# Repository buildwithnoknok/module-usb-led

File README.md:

# noknok LEDs

A USB-controlled ring of 8 WS2812b RGB LEDs for the noknok ecosystem. The Raspberry Pi
Pico drives it as a **USB host**; it can also be driven directly from a PC.

## Features
- 8× WS2812b RGB LEDs (ring)
- CH32V203G6U6 microcontroller, USB 1.1 (CDC) device
- USB-C power + data; 2× Qwiic / STEMMA QT compatible I2C pass-through connectors
- **Unique per-unit USB serial** derived from the chip UID — so the Conductor can tell
  identical modules apart and map them to roles (the USB counterpart of the I2C UID)
- Rich control: per-LED colour/brightness/timed-off in one command, plus 6 built-in
  animations (rainbow, breathe, theatre chase, colour wipe, twinkle, sundown)

## Status
- **Firmware: v1.8.2 — complete** (see [firmware/readme.md](firmware/readme.md) for the
  full command protocol, flashing instructions, and version history)
- Hardware: v1.0

## How it's controlled

### From a Raspberry Pi Pico (USB host) — the noknok Conductor
The Pico hosts the module over PIO-USB (D+ → GP16, D− → GP17, behind a **powered** hub
such as the DataHub). The `NoknokLEDs` driver lives in
[`brain-Pico/software/noknok_usb.py`](https://github.com/buildwithnoknok/brain-Pico/tree/main/software)
and is discovered by the Conductor:

```python
from noknok import Conductor

c = Conductor()
c.enumerate_usb()          # brings up the USB host port, finds all LED modules
# (use c.enumerate_all() for a product that mixes I2C + USB modules)

leds = c.leds[0]                                  # or c.by_uid("<serial>"), or c.role["lamp"]
leds.set_all(255, 0, 0)                           # all red
leds.set_pixel(3, 0, 255, 0)                      # LED 3 green
leds.set_brightness(128)                          # global brightness
leds.set_led(0xFF, 0, 0, 255, brightness=200, duration_ms=1000)  # all blue 1 s, then off
leds.play_preset(leds.PRESET_RAINBOW, speed=40)  # non-blocking animation on the module
leds.play_preset(leds.PRESET_SUNDOWN, speed=30, r=0, g=0, b=255)  # 30 min fade to off, blue
leds.off()
```

Each module carries a unique serial, so multiple LED modules on one hub are addressed
individually. See **[Ecosystem → enumeration.md](https://github.com/buildwithnoknok/Ecosystem/blob/main/software/enumeration.md)**
(USB Module Discovery & Identity) and **[roles.md](https://github.com/buildwithnoknok/Ecosystem/blob/main/software/roles.md)**
(role assignment — this is an *output* module, assigned by cue-and-confirm).

### From a PC
PowerShell / Python helpers in [`tools/`](tools) (`noknok_leds.ps1`, `noknok_leds_pc.py`)
auto-detect the module and expose the same commands.

## Repository Structure
- `/hardware` — KiCad files, schematics, 3D models
- `/firmware` — source (`src/`), built binaries (`bin/`), and the firmware change record (`readme.md`)
- `/tools` — PC control scripts

---

## Trademarks

**noknok** is a registered trademark in Switzerland (Swissreg 1300007033).

Qwiic is a registered trademark of SparkFun Electronics, Inc. STEMMA QT is a
trademark of Adafruit Industries, LLC. Both are named here only to state
connector compatibility - noknok is not affiliated with, endorsed by, or
sponsored by either company.

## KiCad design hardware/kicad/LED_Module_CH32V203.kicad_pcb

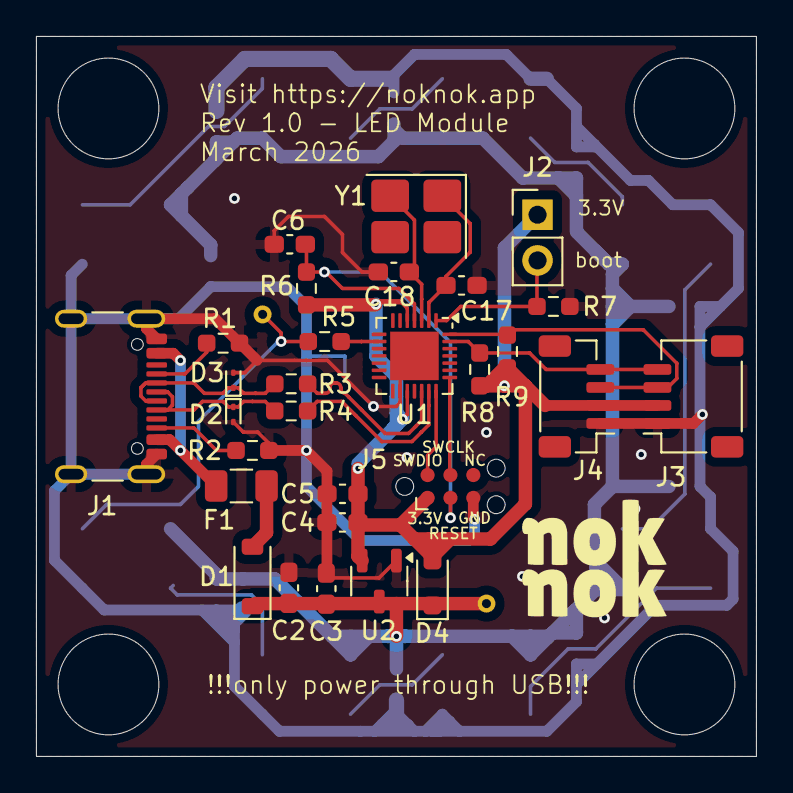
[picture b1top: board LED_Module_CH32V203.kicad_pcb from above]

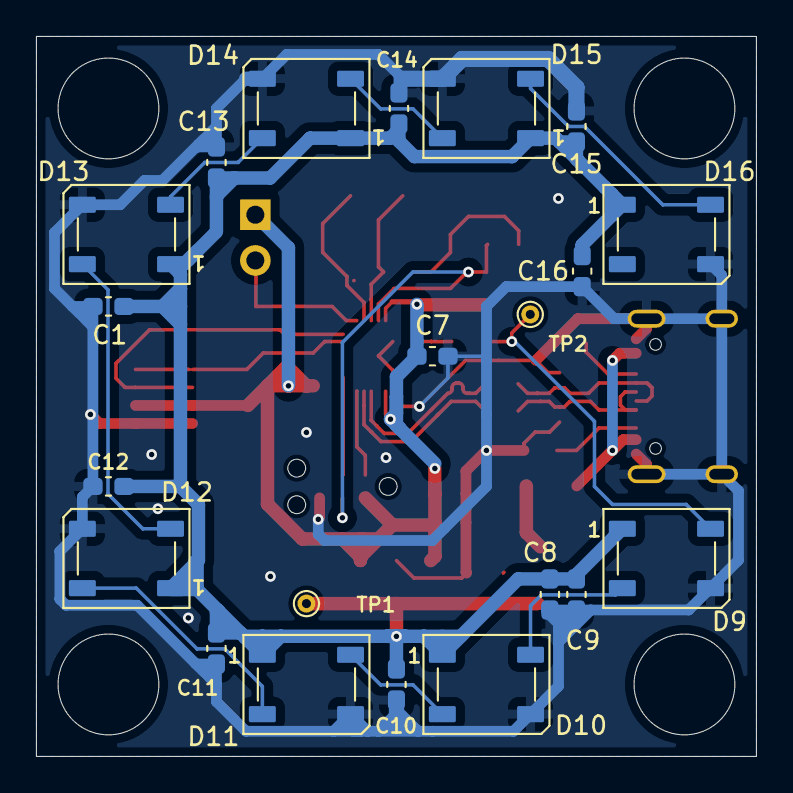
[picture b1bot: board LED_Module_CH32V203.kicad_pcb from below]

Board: 2 copper layers, 40.0 x 40.0 mm, 50 parts (21 on the bottom side), 26 nets.

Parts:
C1, C2, C5, C8: 10uF; C_0603_1608Metric_Pad1.08x0.95mm_HandSolder
C3, C4, C7: 1uF; C_0603_1608Metric_Pad1.08x0.95mm_HandSolder
C6, C9, C10, C11, C12, C13, C14, C15, C16: 0.1uF; C_0603_1608Metric_Pad1.08x0.95mm_HandSolder
C17, C18: 18pF; C_0603_1608Metric_Pad1.08x0.95mm_HandSolder
D1: 1N4007; D_SOD-123
D2, D3: ESD9B5.0ST5G; D_SOD-923
D4: D_Schottky; D_SOD-323_HandSoldering
D9, D10, D11, D12, D13, D14, D15, D16: WS2812B; LED_WS2812B_PLCC4_5.0x5.0mm_P3.2mm
F1: Resettable Polyfuse; Fuse_1206_3216Metric
J1: USB_C_Receptacle_USB2.0_16P; USB_C_Receptacle_GCT_USB4105-xx-A_16P_TopMnt_Horizontal
J2: Jumper Cap; PinHeader_1x02_P2.54mm_Vertical
J3: Qwiic / StemmaQT Connector; JST_SH_SM04B-SRSS-TB_1x04-1MP_P1.00mm_Horizontal_CHRIS
J4: Qwiic / StemmaQT Connector; JST_SH_BM04B-SRSS-TB_1x04-1MP_P1.00mm_Vertical
J5: TagConnect_TC2030; Tag-Connect_TC2030-IDC-NL_2x03_P1.27mm_Vertical
R1, R2: 5.1k; R_0603_1608Metric_Pad0.98x0.95mm_HandSolder
R3, R4: 22R; R_0603_1608Metric_Pad0.98x0.95mm_HandSolder
R5: 100R; R_0603_1608Metric_Pad0.98x0.95mm_HandSolder
R6, R7: 10k; R_0603_1608Metric_Pad0.98x0.95mm_HandSolder
R8, R9: 4.7k; R_0603_1608Metric_Pad0.98x0.95mm_HandSolder
TP1, TP2: TestPoint; TestPoint_THTPad_D1.0mm_Drill0.5mm
U1: CH32V203G6U6; WQFN-28-1EP_4x4mm_P0.4mm_EP2.7x2.7mm
U2: XC6206P332MR; SOT-23-3
Y1: Crystal; Crystal_SMD_3225-4Pin_3.2x2.5mm_HandSoldering

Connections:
+3.3V: C4.1, C5.1, C7.1, D4.2 (A), J2.1, J3.2, J4.2, J5.1 (VCC), R6.2, R8.2, R9.2, U1.5 (VDDA), U1.17 (VDD), U2.2 (VO)
+4.1V: C1.1, C2.1, C3.1, C8.1, C9.1, C10.1, C11.1, C12.1, C13.1, C14.1, C15.1, C16.1, D1.1 (K), D4.1 (K), D9.1 (VDD), D10.1 (VDD), D11.1 (VDD), D12.1 (VDD), D13.1 (VDD), D14.1 (VDD), D15.1 (VDD), D16.1 (VDD), TP1.1, U2.3 (VI)
+5V: D1.2 (A), F1.1
D+: D2.1 (A1), J1.A6 (D+), J1.B6 (D+), R4.1, R4.2, U1.20 (PA12/USB_D+)
D-: D3.1 (A1), J1.A7 (D-), J1.B7 (D-), R3.1, R3.2, U1.19 (PA10/PA11/USB_D-)
GND: C1.2, C2.2, C3.2, C4.2, C5.2, C6.1, C7.2, C8.2, C9.2, C10.2, C11.2, C12.2, C13.2, C14.2, C15.2, C16.2, C17.1, C18.1, D2.2 (A2), D3.2 (A2), D9.3 (VSS), D10.3 (VSS), D11.3 (VSS), D12.3 (VSS), D13.3 (VSS), D14.3 (VSS), D15.3 (VSS), D16.3 (VSS), J1.A1 (GND), J1.A12 (GND), J1.B1 (GND), J1.B12 (GND), J1.S1 (SHIELD), J3.1, J4.1, J5.5 (GND), R1.1, R2.1, R7.2, U1.16 (VSS), U1.29 (VSS), U2.1 (GND)
unnamed: D9.4 (DIN), R5.1, TP2.1
unnamed: D9.2 (DOUT), D10.4 (DIN)
unnamed: D10.2 (DOUT), D11.4 (DIN)
unnamed: D11.2 (DOUT), D12.4 (DIN)
unnamed: D12.2 (DOUT), D13.4 (DIN)
unnamed: D13.2 (DOUT), D14.4 (DIN)
unnamed: D14.2 (DOUT), D15.4 (DIN)
unnamed: D15.2 (DOUT), D16.4 (DIN)
unnamed: F1.2, J1.A4 (VBUS), J1.A9 (VBUS), J1.B4 (VBUS), J1.B9 (VBUS)
unnamed: J1.A5 (CC1), R1.2
unnamed: J1.B5 (CC2), R2.2
unnamed: J2.2, R7.1, U1.1 (BOOT0/PB8)
unnamed: J3.3, J4.3, R9.1, U1.28 (PB7)
unnamed: J3.4, J4.4, R8.1, U1.27 (PB6)
unnamed: J5.4 (SWCLK), U1.22 (PA14/SWCLK)
unnamed: J5.2 (SWDIO), U1.21 (PA13/SWDIO)
unnamed: C6.2, J5.3 (~RESET), R6.1, U1.4 (~RST)
unnamed: C17.2, U1.2 (OSC_IN/PD0), Y1.1
unnamed: C18.2, U1.3 (OSC_OUT/PD1), Y1.2
unnamed: R5.2, U1.9 (PA3)

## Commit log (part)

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2026-05-08 Create hardware folder
2026-05-08 Create firmware folder
2026-05-08 Create docs folder
2026-05-08 Create hardware/kicad folder
2026-05-08 Create firmware/src folder
2026-05-08 Create firmware/bin folder
2026-06-01 Update product name to # noknok LEDs
2026-06-02 Add firmware v1.0 and PC helper
2026-06-02 Fix ws_show: replace ISR with polling (DMA TC flag)
2026-06-02 Fix USB: use 144MHz HSI (fsusb requires 144/96/48MHz), fix WS2812b timing
2026-06-02 Fix: enable AFIO clock (PA3 AF), add SWEVGR trigger, remove boot flash for USB test
2026-06-02 firmware: v1.1 - interrupt DMA, 144 MHz, AFIO fix, boot flash
2026-06-02 firmware: update hex to v1.1
2026-06-04 firmware v1.4: switch to USBD/FSDEV + manual HSE clock - USB now enumerates
2026-06-04 firmware v1.4: USBD CDC descriptors (VID 1209/PID 4E4E)
2026-06-04 firmware v1.4: HSI boot + manual 48MHz clock, USBD
2026-06-04 firmware v1.4: build with usbd.c
2026-06-04 firmware v1.4: compiled hex (USBD, enumerates)
2026-06-04 tools: add led_test.ps1 (raw-handle COM test - works around PowerShell SerialPort)
2026-06-04 tools: rewrite noknok_leds_pc.py - full PC driver (auto-detect, API, animations, CLI)
2026-06-04 tools: add noknok_leds.ps1 - PowerShell driver (raw handle, auto-detect, verified working)
2026-06-09 Preserve optional ch32fun CH32V203 clock patches (dev reference)
2026-06-17 firmware: add v1.4 binary (bin/noknok_leds.bin) for WCHISPTool flashing
2026-06-17 firmware: add firmware/readme.md with Firmware Change Record
2026-06-17 tools: fix noknok_leds.ps1 zero-arg parse error (list/off/rainbow)
2026-06-17 firmware v1.5: add 0xB1 GET_VERSION command (noknok standard) -> [PROTO,MAJ,MIN,PAT]
2026-06-17 firmware v1.5: rebuilt hex (adds GET_VERSION)
2026-06-17 firmware v1.5: rebuilt bin (adds GET_VERSION)
2026-06-17 firmware: change record - add v1.5 (GET_VERSION), relabel abandoned CDC experiment
2026-06-17 tools: add 'version' and 'id' commands to PowerShell driver (reads 0xB1/0xF0 reply)
2026-06-17 tools: add version() method + 'version' CLI to Python driver (0xB1)
2026-06-23 chore: remove redundant firmware/.keep (folder now has content)
2026-06-23 chore: remove redundant firmware/bin/.keep (folder now has content)
2026-06-23 chore: remove redundant firmware/src/.keep (folder now has content)
2026-06-23 chore: remove redundant hardware/kicad/.keep (folder now has content)
